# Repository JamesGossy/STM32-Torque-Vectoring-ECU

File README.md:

<div align="center">

# STM32 Torque Vectoring ECU

**Firmware for a four-motor torque vectoring and derating ECU on an STM32G474.**

*A lap of the Formula Student Germany 2024 track in the full-physics simulation this ECU
grew out of. Blue and yellow dots are cones, cyan is the racing line, the red box is the car.*

</div>

---

## What it does

The ECU sits on the car's CAN bus with four STM32 motor controllers (one per wheel,
from the STM32-Motor-Controller project). Every 10 ms it:

1. reads the driver's pedals and steering, its own IMU, and each controller's speed,
   temperature and bus voltage,
2. decides whether torque is allowed at all (startup, faults, plausibility checks),
3. works out how much torque the motors may give right now (derating),
4. splits the driver's torque request across the four wheels to help the car turn
   (torque vectoring),
5. sends each controller its current setpoint over CAN.

It can also run in **HIL mode**, where the Formula Student simulator stands in for
the car. The simulator sends steering, torque request, yaw rate and wheel speeds over
CAN, and reads back the torque the ECU commanded. The real motor controllers on the
bench take part exactly as they would on the car.

Battery management is out of scope for now: the bench runs from a lab power supply.

```mermaid
flowchart LR
    pedals["Pedals & steering"] -->|analog| ecu
    imu["IMU (LSM6DSV16X)"] -->|SPI| ecu
    ecu["Torque vectoring ECU<br/>STM32G474"]
    ecu <-->|"CAN 1 Mbit/s<br/>current setpoints / telemetry"| mc["Four motor controllers<br/>FL · FR · RL · RR"]
    sim["Formula Student sim<br/>(HIL mode)"] <-->|"CAN via CANable<br/>steering, torque request,<br/>yaw rate, wheel speeds"| ecu
    usb["PC console"] <-->|USB-C| ecu

    classDef controller fill:#eef2ff,stroke:#6366f1,color:#1e1b4b
    classDef drive fill:#ecfdf5,stroke:#059669,color:#064e3b
    classDef interface fill:#fff7ed,stroke:#ea580c,color:#7c2d12
    class ecu controller
    class mc,pedals,imu drive
    class sim,usb interface
```

## Repository layout

```
ECU_Hardware/            KiCad schematics and PCB, board requirements, sensor pinout
docs/                    pictures from the earlier full-physics simulation
ECU_Firmware/
  app/                   the application, no hardware access (runs on the board and the PC)
    app.c                100 Hz control step and the drive state machine
    torque_vectoring.c   the yaw-rate torque vectoring law
    derate.c             torque limits from temperature, speed and bus voltage
    driver_inputs.c      pedals and steering, with the Formula Student plausibility rules
    motors.c             the motor controller CAN protocol, client side
    hil.c                inputs from the HIL simulator
    imu.c, gps.c         LSM6DSV16X gyro/accel driver, NMEA reader
    console.c            USB text console
    config.h             every number: car, sensors, limits, derating thresholds
    can_protocol.h       every CAN message (shared with the simulator)
  hal/hal.h              what the app needs from a board
  hal/stm32g474/         register-level drivers: clocks, ADC+DMA, SPI, UART, FDCAN, USB
  sim/                   the board in memory, and ecu_sim for simulator runs
  tests/                 unit and whole-application tests
Makefile                 shortcuts for the CMake builds, tests and formatting
```

The application only ever talks to `hal.h`. On the board that is the STM32 drivers;
on a PC it is `sim/sim.c`. The same application code is what gets tested, what runs in
the simulator, and what runs on the car.

## Torque vectoring

The steering angle and speed give the yaw rate the driver is asking for (a bicycle
model). The gyro gives the yaw rate the car really has. The difference moves torque
from one side of the car to the other:

```
base            = request / 4, inside the derated limits
target yaw rate = speed * tan(steering * 0.23) / wheelbase
correction      = 4 Nm per rad/s * (target - measured), at most 4 Nm,
                  and never more than the room both sides have left
left wheels     = base - correction
right wheels    = base + correction
```

The total torque never changes, only how it is shared. It works under regen too. The
law and gains are the same as the simulator's own software torque vectoring, so an HIL
lap can be compared directly with a pure simulation lap.

This is what it looks like on a car. Both pictures come from the full-physics simulation
this project started as, which used a grip-aware PID version of the same idea. At the
hairpin the outer wheels drive and the inner wheels regen, which swings the car round:

<div align="center">

</div>

Through a corner the four wheel torques start together, then fan apart as each wheel is
given its own share:

<div align="center">

</div>

## Derating

One factor covers the whole car, so derating never adds a yaw moment of its own.

| Input | Starts at | Zero torque at | Limits |
| --- | --- | --- | --- |
| Controller FET temperature | 80 C | 95 C (controllers trip at 100 C) | drive and regen |
| ECU board temperature | 70 C | 85 C | drive and regen |
| Motor speed (from the controllers) | 70 % of 10k rpm | 10k rpm | drive |
| Bus voltage, sagging | 14 V | 10 V (controllers trip at 8 V) | drive |
| Bus voltage, rising | 50 V | 56 V (controllers trip at 60 V) | regen |
| Car speed | 2 m/s | standstill | regen |

Regen fades out as the car stops, because at standstill a regen request would drive the
motors backwards. The rising-bus limit matters on the bench: a lab supply cannot absorb regen, so the bus
voltage climbs. The speed limit uses the speed the controller measures, because that
protects the real motor. An unloaded bench motor settles just under its limit instead of
running away. All thresholds are in `config.h`.

## When torque is allowed

| State | Meaning |
| --- | --- |
| `STARTUP` | first second: the gyro bias is measured, so the car must be still |
| `STANDBY` | ready, no torque. Controllers are kept idle |
| `DRIVE` | torque is sent every 10 ms |
| `FAULT` | latched after a hard stop while driving. No torque until `clear` on the console or a power cycle |

To arm, press the brake with the throttle released and hold it for 1 s in standby (a
stand-in until the car has a ready-to-drive button). After any disarm the brake has to be
lifted and pressed again. In HIL mode the simulator arms it instead, with a fresh drive
request. Arming needs every
controller online and healthy, main power present (so the pedal sensors are powered), a
working IMU and a healthy CAN bus.

Any of those failing while driving latches `FAULT` and keeps the cause in the status frame, so a flickering fault cannot re-arm the car. Two pedal problems
only zero the torque while they last, as the Formula Student rules ask:

- **Throttle sensor disagreement:** the two throttle sensors differ by more than 10 %
  for over 100 ms.
- **Brake with throttle:** the brake and more than 25 % throttle are pressed together.
  Torque stays at zero until the throttle drops below 5 %.

Torque only goes out once all four controllers are running, so one side can never drive
alone. On disarm the ECU sends zero current and an idle request to every controller at
once, and keeps sending zero current while disarmed. The controllers also stop by
themselves 250 ms after their setpoints stop, so a crashed or unplugged ECU is safe. The
watchdog resets the ECU after 100 ms.

## Steering wheel panel

The panel is a CAN node (17) that sends three dial values: torque vectoring strength,
drive power and regen. They scale the yaw correction and the drive and regen torque
limits, on top of derating. Without a panel everything stays at 100 %. If the panel goes
quiet the last values are kept, so a lost cable never raises a limit. The panel lights
its LEDs from the ECU's `STATUS` frame (state and inhibit bits). The console `status`
line shows the dial values.

## CAN bus

Classic CAN at 1 Mbit/s, 11-bit ids of the form `(node << 5) | message`, the scheme the
motor controllers already use. Floats are little endian. The full list is in
[`can_protocol.h`](ECU_Firmware/app/can_protocol.h).

| Node | Who | Messages |
| --- | --- | --- |
| 1 to 4 | motor controllers FL, FR, RL, RR | ECU sends `SET_STATE`, `SET_IQ`. They send heartbeat, iq and speed, bus volts and temperature |
| 16 | this ECU | `STATUS` (state, inhibit bits, derating) and `YAW` (target and measured) every 10 ms |
| 17 | steering wheel panel | `DIALS`: torque vectoring %, drive power %, regen % (0 to 100) |
| 16 | HIL simulator | `DRIVER`, `WHEELS_F`, `WHEELS_R`, then `CONTROL` last each tick |

Wheel torque is sent as controller current: 1.47 Nm per amp maps the car motor's 29.4 Nm
onto the controller's 20 A limit. The left motors are mounted mirrored, so their current
has the opposite sign. Set each controller's node id from its own console with `node <id>`.

## Build, flash and test

Needs CMake and Ninja, plus `arm-none-eabi-gcc` for the board (STM32CubeCLT has all
three) and a host C compiler for the tests.

```
make firmware     # ECU_Firmware/build/tv_ecu.elf, .hex and .bin
make flash        # over SWD with an ST-LINK and STM32CubeProgrammer
make test         # unit tests and whole-application tests on the PC
make test MC_DIR=../STM32-Motor-Controller/controller_firmware   # also the controller interop test
```

The interop test builds the real motor controller firmware for the PC and runs it
against this ECU. It checks that the ECU arms the controller, that the controller follows
the commanded current, that speed derating holds a free motor near its limit, and that
the controller stops when drive is switched off and when the ECU goes away.

## USB console

Plug in USB-C and open the virtual COM port with any terminal.

| Command | Does |
| --- | --- |
| `status` | state, inputs, torques, derating and any inhibit reasons |
| `stream on` / `stream off` | the status line every 100 ms |
| `motors` | one line per motor controller |
| `gps` | the latest GPS fix |
| `off` | stop sending torque |
| `clear` | ask every controller to clear its faults |
| `estop` | broadcast the controller e-stop |

## HIL testing with the Formula Student simulator

```
PC: Formula Student sim --TCP-- can_bridge.py --USB-- CANable 2.0 --CAN-- ECU board
                                                                    \-- motor controllers
```

1. Wire the CANable, the ECU and the motor controllers on one bus, terminated at both
   ends (the ECU has fixed split termination). Power the ECU and controllers from the
   bench supply.
2. Calibrate each motor controller and give it its node id (1 FL, 2 FR, 3 RL, 4 RR).
   Controllers you do not have are played by the simulator.
3. Start the bridge, with the CANable's COM port:
   `python tools/can_bridge.py --channel COM5`
4. Run the simulator with `HIL=1`, for example `HIL=1 python visualiser.py` or
   `HIL=1 make eval` in the simulator repo.

The simulator listens for 0.3 s to find which controllers are real, waits for the ECU to
reach standby, arms it, then drives. It drives the car model with the current the ECU
commanded; set `HIL_TORQUE=measured` to use the current the real controllers report
instead (useful with loaded motors). `HIL_FET_TEMP` and `HIL_BUS_V` change what the
simulated controllers report, to try derating.

Without any hardware, `ecu_sim` (built by `make sim`) plays the ECU on the PC and the
simulator talks to it in lock-step. The simulator's `make test-hil` runs its whole lap
matrix that way.

### Driverless mode

Set `HIL_AUTONOMY=ecu` in the simulator and the ECU does the driving. The simulator sends
the nearest 16 cones (range in cm, bearing in mrad, colour) as `HIL_MSG_CONE` frames, one
per cone, ahead of each `CONTROL` frame. Every 10 ms the ECU turns them into a centre line
(`app/planner.c`), steers with pure pursuit and sets the total torque request with a
proportional speed controller (`app/autonomy.c`), then sends the result back in
`ECU_MSG_COMMAND`. Torque vectoring, derating and the state machine work as before.

| Runs on the ECU | Runs on the PC |
| --- | --- |
| Cone gating and midpoints, pure pursuit, speed control, steering rate limit | Vehicle model, cone sensor, EKF-SLAM (display only) |

If complete cone scans stop arriving for 50 ms the ECU latches FAULT (`cones-lost`), like
any other hard stop. The planner and controller are a port of the simulator's own, with
fixed constants in `config.h`, so laps match the simulator's software autopilot only at
its default tunables. `make test-hil` in the simulator repo checks this.

**On the bench:** the motors are unloaded, so any torque spins them up until speed
derating holds them just under 10k rpm. Keep them guarded and clamped down.

## Not done yet

- Battery and BMS messages, and derating from state of charge.
- Pedal and steering calibration stored in flash (it is in `config.h` for now).
- A ready-to-drive button input.
- GPS is read and shown on the console, but not used by the controller.
- The IMU interrupt pin and the GPS PPS pin are wired but not used.

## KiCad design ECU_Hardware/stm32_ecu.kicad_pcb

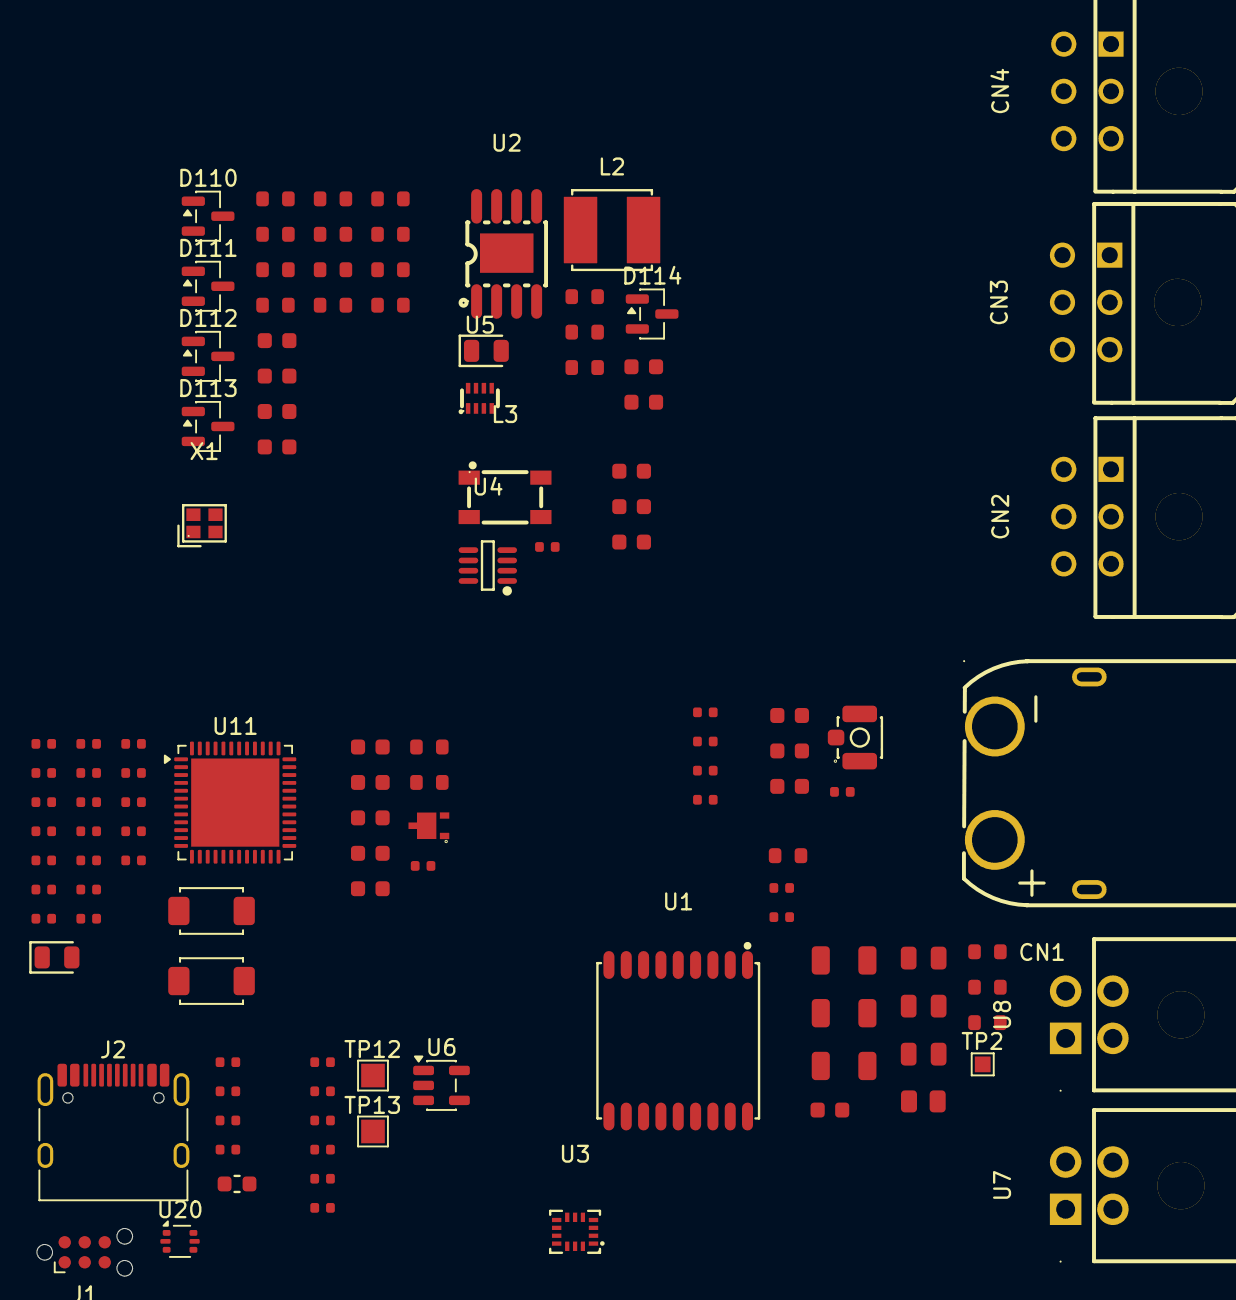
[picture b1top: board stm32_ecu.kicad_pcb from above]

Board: 2 copper layers, 118 parts (0 on the bottom side), 69 nets, no tracks yet.

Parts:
C1: 100nF; C_0805
C2, C7, C37, C42, C45, C50, C93: 1uF; C_0402
C5, C92, C101, C102, C120, C121, C122, C124: 100nF; C_0603
C6, C26, C32, C44: 100pF; C_0603
C8, C9, C11, C12, C20, C21, C22, C23, C28, C38, C39, C52: 100nF; C_0402
C10, C43: 15pF; C_0402
C15: 4.7uF; C_0402
C30, C34, C35: 4.7uF; C_1206
C54, C55: 2.2uF; C_0402
C58, C79: 22uF; C_0805
C100: 10uF; C_0603
C110, C111, C112, C113: 10nF; C_0603
C123: 22uF; C_0603
CN1: XT60PW-M; CONN-TH_XT60PW-M
CN2, CN3, CN4: XDWF-C3030WR-2*3P; CONN-TH_XDWF-C3030WR-2X3P
D9: ESDCAN03-2BWY; DFN2020-3_L2.0-W2.0-P1.30-BR-1
D14, D15: White; D_0805
D110, D111, D112, D113, D114: BAT54S; SOT-23
FB1, FB2: 600Ω; R_0402
FB3: 120Ω @100MHz; FB_0603
J1: TC2030-NL; Tag-Connect_TC2030-IDC-NL_2x03_P1.27mm_Vertical
J2: USB_C_Receptacle_USB2.0_16P; USB_C_Receptacle_HRO_TYPE-C-31-M-12
J3: U.FL; IPEX-SMD_BWIPX-1-001E
L2: SWPA5040S150MT; IND-SMD_L5.0-W5.0
L3: ACT45B-101-2P-TL003; FILTER-SMD_4P-L4.5-W3.2-TL_ACT45B
L4: 47nH; L_0402
R1: 220kΩ; R_0603
R2, R5, R16: 10kΩ; R_0402
R3: 39kΩ; R_0402
R4, R26: 10kΩ; R_0603
R8: 200Ω; R_0402
R18, R19: 22Ω; R_0402
R23, R51: 100kΩ; R_0402
R25: 40.2kΩ; R_0603
R27: 64.9kΩ; R_0603
R29, R30: 5.1kΩ; R_0402
R38: 100kΩ; R_0805
R64, R65: 60.4Ω; R_0603
R110, R113, R116, R119: 33kΩ; R_0603
R111, R114, R117, R120: 47kΩ; R_0603
R112, R115, R118, R121, R130: 1kΩ; R_0603
S1, S2: Tactile Button, 160gf; SW_TS-1088-AR02016
TH1: 10k NTC; R_0603
TP2: 5V; TestPoint_Pad_1.0x1.0mm
TP12, TP13: TestPoint; TestPoint_Pad_1.5x1.5mm
U1: ATGM336H-5N31; GPSM-SMD_ATGM336H-TR
U2: LMR38020SQDDARQ1; SOIC-8_L4.9-W3.9-P1.27-LS6.0-BL-EP3.4
U3: LSM6DSV16XTR; LGA-14_L3.0-W2.5-P0.50-BR
U4: TCAN337GDCNR; SOT-23-8_L3.0-W1.7-P0.65-LS2.8-BR
U5: LM66200DRLR; SOT-583-8_L2.1-W1.2-P0.50-LS1.6-BL
U6: AP2112K-3.3; SOT-23-5
U7, U8: XD-43045-2*2AW; CONN-TH_4P-P3.00_XUNDA_XD-43045-2_2AW
U11: STM32G474CEUx; QFN-48-1EP_7x7mm_P0.5mm_EP5.6x5.6mm
U20: USBLC6-2P6; SOT-666
X1: XC7EL89COO-114YLC-16M; CRYSTAL-SMD_4P-L2.0-W1.6-BL

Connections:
5V_OR: C45.1, TP12.1 (1_1), U5.2 (VOUT), U5.7 (VOUT), U6.1 (VIN), U6.3 (EN)
+3V3: C7.1, C9.1, C11.1, C12.1, C15.1, C20.1, C21.1, C22.1, C23.1, C93.1, C100.1, C101.1, C102.1, D110.2 (K), D111.2 (K), D112.2 (K), D113.2 (K), D114.2 (K), FB1.1, J1.1 (VCC), R2.1, R3.1, R5.2, R23.1, R130.1, S2.1 (A), TP13.1 (1_1), U1.6 (VBAT), U1.8 (VCC), U3.5 (Vdd_IO), U3.8 (Vdd), U4.3 (Vcc), U6.5 (VOUT), U11.1 (VBAT), U11.23 (VDD), U11.35 (VDD), U11.48 (VDD)
+5V_BUCK: C37.1, C58.1, C79.1, C123.1, L2.2, R25.1, R38.1, TP2.1 (1_1), U5.6 (VIN2)
+5V_USB: C42.1, C55.1, FB3.2, U5.3 (VIN1)
/APPS_1: C110.1, D110.3 (COM), R112.2, U11.9 (PA1)
/APPS_1_RAW: CN2.3, R110.1
/APPS_2: C111.1, D111.3 (COM), R115.2, U11.10 (PA2)
/APPS_2_RAW: CN2.6, R113.1
/BPPS: C112.1, D112.3 (COM), R118.2, U11.11 (PA3)
/BPPS_RAW: CN3.3, R116.1
/CAN_FAULT: R5.1, U4.5 (FAULT), U11.42 (PB4)
/CAN_RX: U4.4 (RXD), U11.43 (PB5)
/CAN_TX: U4.1 (TXD), U11.44 (PB6)
/CAN_UNFIL_N: C44.1, L3.3, R65.1, U7.2, U8.2
/CAN_UNFIL_P: C32.2, L3.4, R64.1, U7.1, U8.1
/Connectors/APPS_5V: C120.1, CN2.1, CN2.4
/Connectors/BPPS_5V: C121.1, CN3.1, CN3.4
/Connectors/CC1: J2.A5 (CC1), R30.1
/Connectors/CC2: J2.B5 (CC2), R29.1
/Connectors/D+: J2.A6 (D+), J2.B6 (D+), U20.1 (I/O2)
/Connectors/D-: J2.A7 (D-), J2.B7 (D-), U20.6 (I/O1)
/Connectors/STEERING_5V: C122.1, CN4.1, CN4.4
/Connectors/USB_VBUS: C54.1, FB3.1, J2.A4 (VBUS), J2.A9 (VBUS), J2.B4 (VBUS), J2.B9 (VBUS), U20.5 (VBUS)
/GPS/GPS_ANT_BIAS: L4.2, U1.14 (VCC_RF)
/GPS_PPS: U1.4 (1PPS), U11.30 (PA8)
/GPS_RX: U1.2 (TXD), U11.32 (PA10)
/GPS_TX: U1.3 (RXD), U11.31 (PA9)
/IMU_CS_N: R2.2, U3.12 (CS), U11.12 (PA4)
/IMU_INT: U3.4 (INT1), U11.16 (PC4)
/IMU_MISO: U3.1 (SDO/SA0), U11.14 (PA6)
/IMU_MOSI: U3.14 (SDA), U11.15 (PA7)
/IMU_SCK: U3.13 (SCL), U11.13 (PA5)
/MCU/BOOT0: R16.1, S2.2 (B), U11.46 (PB8)
/MCU/HEARTBEAT: R8.1, U11.47 (PB9)
/MCU/HSE_IN: C43.1, U11.5 (PF0), X1.3
/MCU/HSE_OUT: C10.1, U11.6 (PF1), X1.1
/Power Regulation/ON: R51.1, U5.4 (~ON)
/Power Regulation/PWR_LED_A: D15.2, R130.2
/Power Regulation/ST: R23.2, U5.8 (ST)
/STEERING: C113.1, D113.3 (COM), R121.2, U11.17 (PB0)
/STEERING_RAW: CN4.3, R119.1
/SWCLK: J1.4 (SWCLK), R19.2
/SWDIO: J1.2 (SWDIO), R18.2
/SWO: J1.6 (SWO), U11.41 (PB3)
/TEMP_SENSE: C8.1, R3.2, TH1.1, U11.8 (PA0)
/USB_D+: U11.34 (PA12), U20.3 (I/O2)
/USB_D-: U11.33 (PA11), U20.4 (I/O1)
/VIN_12_60V: C1.1, C30.1, C34.1, C35.1, CN1.2 (+), R1.1, U2.2 (EN), U2.3 (VIN)
/VIN_SENSE: C124.1, D114.3 (COM), R1.2, R4.1, U11.18 (PB1)
/nRST: C52.1, J1.3 (~RESET), S1.2 (B), U11.7 (PG10)
GND: C1.2, C2.2, C5.1, C6.1, C7.2, C8.2, C9.2, C10.2, C11.2, C12.2, C15.2, C20.2, C21.2, C22.2, C23.2, C26.2, C28.2, C30.2, C32.1, C34.2, C35.2, C37.2, C38.2, C39.2, C42.2, C43.2, C44.2, C45.2, C50.2, C52.2, C54.2, C55.2, C58.2, C79.2, C93.2, C100.2, C101.2, C102.2, C110.2, C111.2, C112.2, C113.2, C120.2, C121.2, C122.2, C123.2, C124.2, CN1.1 (-), CN1.3, CN1.4, CN2.2, CN2.5, CN3.2, CN3.5, CN4.2, CN4.5, D9.3 (K), D14.1, D15.1, D110.1 (A), D111.1 (A), D112.1 (A), D113.1 (A), D114.1 (A), J1.5 (GND), J2.A1 (GND), J2.A12 (GND), J2.B1 (GND), J2.B12 (GND), J2.SH (SHIELD), J3.2 (Ext), R4.2, R16.2, R26.2, R27.2, R29.2, R30.2, R51.2, R111.2, R114.2, R117.2, R120.2, S1.1 (A), TH1.2, U1.1 (GND), U1.10 (GND), U1.12 (GND), U2.1 (GND), U2.9 (EP), U3.2 (SDx/AH1/Qvar1), U3.3 (SCx/AH2/Qvar2), U3.6 (GND), U3.7 (GND), U4.2 (GND), U4.8 (S), U5.1 (GND), U5.5 (GND), U6.2 (GND), U7.3, U8.3, U11.49 (VSS), U20.2 (GND), X1.2 (GND), X1.4 (GND)
unnamed: C5.2, R64.2, R65.2
unnamed: D14.2, R8.2
unnamed: J3.1 (In), L4.1, U1.11 (RF_IN)
unnamed: R110.2, R111.1, R112.1
unnamed: R113.2, R114.1, R115.1
unnamed: R116.2, R117.1, R118.1
unnamed: R119.2, R120.1, R121.1
unnamed: C92.2, U2.7 (BOOT)
unnamed: R25.2, R26.1, U2.5 (FB)
unnamed: R38.2, U2.6 (PG)
unnamed: R27.1, U2.4 (RT/SYNC)
unnamed: C92.1, L2.1, U2.8 (SW)
unnamed: C6.2, D9.1 (A), L3.1, U4.7 (CANH)
unnamed: C26.1, D9.2 (A), L3.2, U4.6 (CANL)
unnamed: R18.1, U11.36 (PA13)
unnamed: R19.1, U11.37 (PA14)
VDDA: C2.1, C28.1, C38.1, FB1.2, FB2.2, U11.21 (VDDA)
VREF: C39.1, C50.1, FB2.1, U11.20 (VREF+)

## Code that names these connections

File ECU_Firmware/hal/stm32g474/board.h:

/* Pin map of the ECU board (U11, STM32G474CEU6), taken from ECU_Hardware/schematics.
   PC4 (IMU_INT) and PA8 (GPS_PPS) are wired but not used yet. */
#ifndef BOARD_H
#define BOARD_H

#include "stm32g4xx.h"

/* ---- pin map ----

   PA0 TEMP_SENSE ADC1_IN1    PA4 IMU_CS_N GPIO       PA9  GPS_TX    USART1 AF7
   PA1 APPS_1     ADC1_IN2    PA5 IMU_SCK  SPI1 AF5   PA10 GPS_RX    USART1 AF7
   PA2 APPS_2     ADC1_IN3    PA6 IMU_MISO SPI1 AF5   PB4  CAN_FAULT input
   PA3 BPPS       ADC1_IN4    PA7 IMU_MOSI SPI1 AF5   PB5  CAN_RX    FDCAN2 AF9
   PB0 STEERING   ADC1_IN15   PB9 HEARTBEAT LED       PB6  CAN_TX    FDCAN2 AF9
   PB1 VIN_SENSE  ADC1_IN12   PA11/PA12 USB */

#define LED_PIN       9 // PB9
#define IMU_CS_PIN    4 // PA4
#define CAN_FAULT_PIN 4 // PB4, TCAN337G FAULT goes high on a transceiver fault

enum { PIN_IN, PIN_OUT, PIN_AF, PIN_ANALOG };

static inline void pin_mode(GPIO_TypeDef *port, uint32_t pin, uint32_t mode, uint32_t af)
{
    port->MODER = (port->MODER & ~(3u << (pin * 2))) | (mode << (pin * 2));
    if (mode == PIN_AF) {
        port->OSPEEDR |= 3u << (pin * 2);
        uint32_t shift      = (pin & 7) * 4;
        port->AFR[pin >> 3] = (port->AFR[pin >> 3] & ~(0xFu << shift)) | (af << shift);
    }
}

void board_init(void);

#endif
